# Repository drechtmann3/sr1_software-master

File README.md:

sr1_software
============

All software for SR1

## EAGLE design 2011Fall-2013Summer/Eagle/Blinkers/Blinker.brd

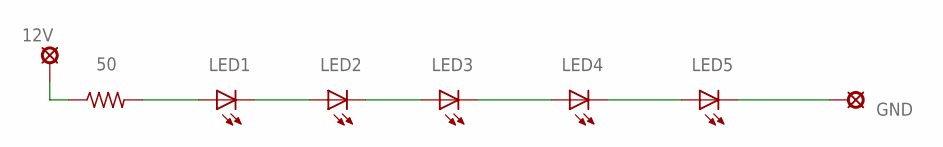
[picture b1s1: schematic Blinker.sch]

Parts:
12V: LSP13
50: RESISTORSMD1206; R1206
GND: LSP13
LED1: LED1; CP41B
LED2: LED2; CP41B
LED3: LED3; CP41B
LED4: LED4; CP41B
LED5: LED5; CP41B

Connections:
GND: GND.MP, LED5.1 (C), LED5.4 (C)
unnamed: 50.2, LED1.2 (A), LED1.3 (A)
unnamed: LED1.1 (C), LED1.4 (C), LED2.2 (A), LED2.3 (A)
unnamed: LED2.1 (C), LED2.4 (C), LED3.2 (A), LED3.3 (A)
unnamed: LED3.1 (C), LED3.4 (C), LED4.2 (A), LED4.3 (A)
unnamed: LED4.1 (C), LED4.4 (C), LED5.2 (A), LED5.3 (A)
unnamed: 12V.MP, 50.1

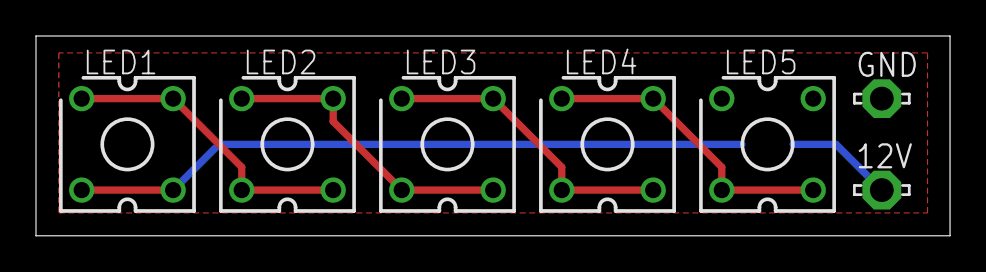
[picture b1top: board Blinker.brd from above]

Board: 2 copper layers, 50.8 x 11.1 mm, 8 parts (1 on the bottom side), 7 nets.

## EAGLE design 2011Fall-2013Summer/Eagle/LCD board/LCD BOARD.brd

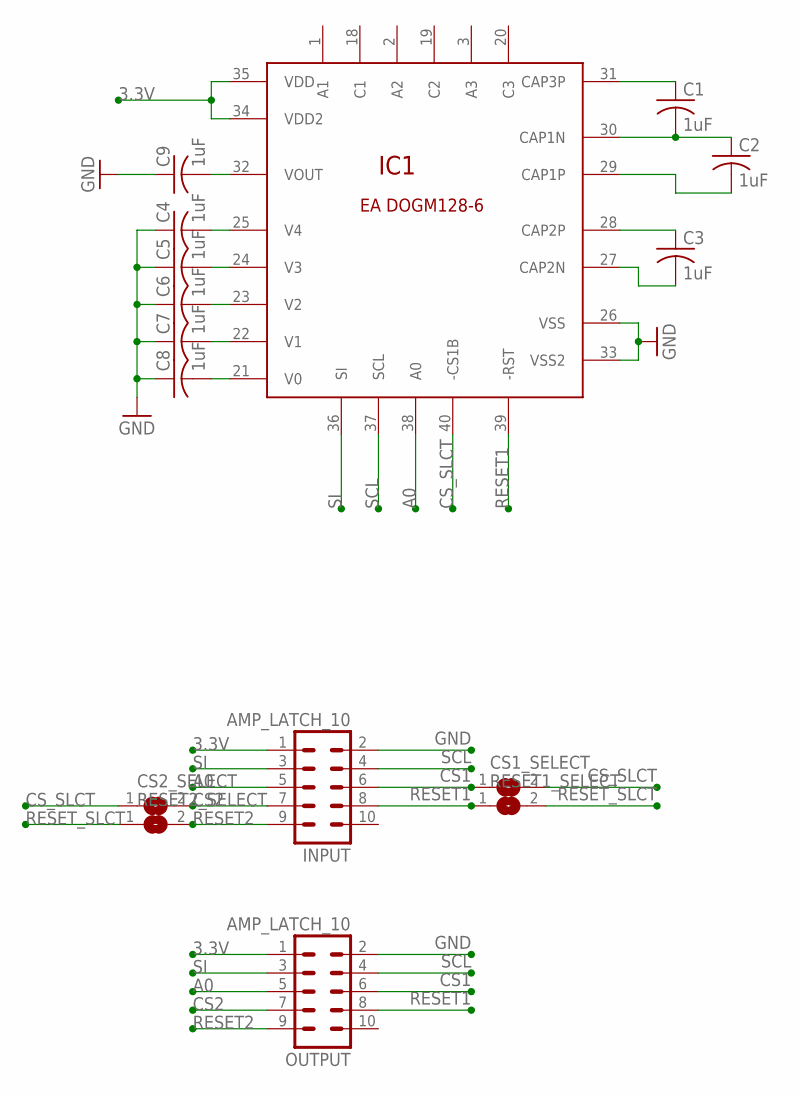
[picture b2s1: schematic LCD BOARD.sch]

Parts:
C1, C2, C3, C4, C5, C6, C7, C8, C9: 1uF; C1206
CS1_SELECT, CS2_SELECT: SJ
IC1: EADOGM128
INPUT: AMP_LATCH_10; MA05-2
OUTPUT: AMP_LATCH_10; MA05-2
RESET1_SELECT, RESET2_SELECT: SJ

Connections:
3.3V: IC1.34 (VDD2), IC1.35 (VDD), INPUT.1, OUTPUT.1
A0: IC1.38 (A0), INPUT.5, OUTPUT.5
CS1: CS1_SELECT.1, INPUT.6, OUTPUT.6
CS2: CS2_SELECT.2, INPUT.7, OUTPUT.7
CS_SLCT: CS1_SELECT.2, CS2_SELECT.1, IC1.40 (-CS1B)
GND: C4.1, C5.1, C6.1, C7.1, C8.1, C9.1, IC1.26 (VSS), IC1.33 (VSS2), INPUT.2, OUTPUT.2
unnamed: C1.2, C2.1, IC1.30 (CAP1N)
unnamed: C1.1, IC1.31 (CAP3P)
unnamed: C2.2, IC1.29 (CAP1P)
unnamed: C3.2, IC1.27 (CAP2N)
unnamed: C3.1, IC1.28 (CAP2P)
unnamed: C9.2, IC1.32 (VOUT)
unnamed: C4.2, IC1.25 (V4)
unnamed: C5.2, IC1.24 (V3)
unnamed: C6.2, IC1.23 (V2)
unnamed: C7.2, IC1.22 (V1)
unnamed: C8.2, IC1.21 (V0)
RESET1: IC1.39 (-RST), INPUT.8, OUTPUT.8, RESET1_SELECT.1
RESET2: INPUT.9, OUTPUT.9, RESET2_SELECT.2
RESET_SLCT: RESET1_SELECT.2, RESET2_SELECT.1
SCL: IC1.37 (SCL), INPUT.4, OUTPUT.4
SI: IC1.36 (SI), INPUT.3, OUTPUT.3

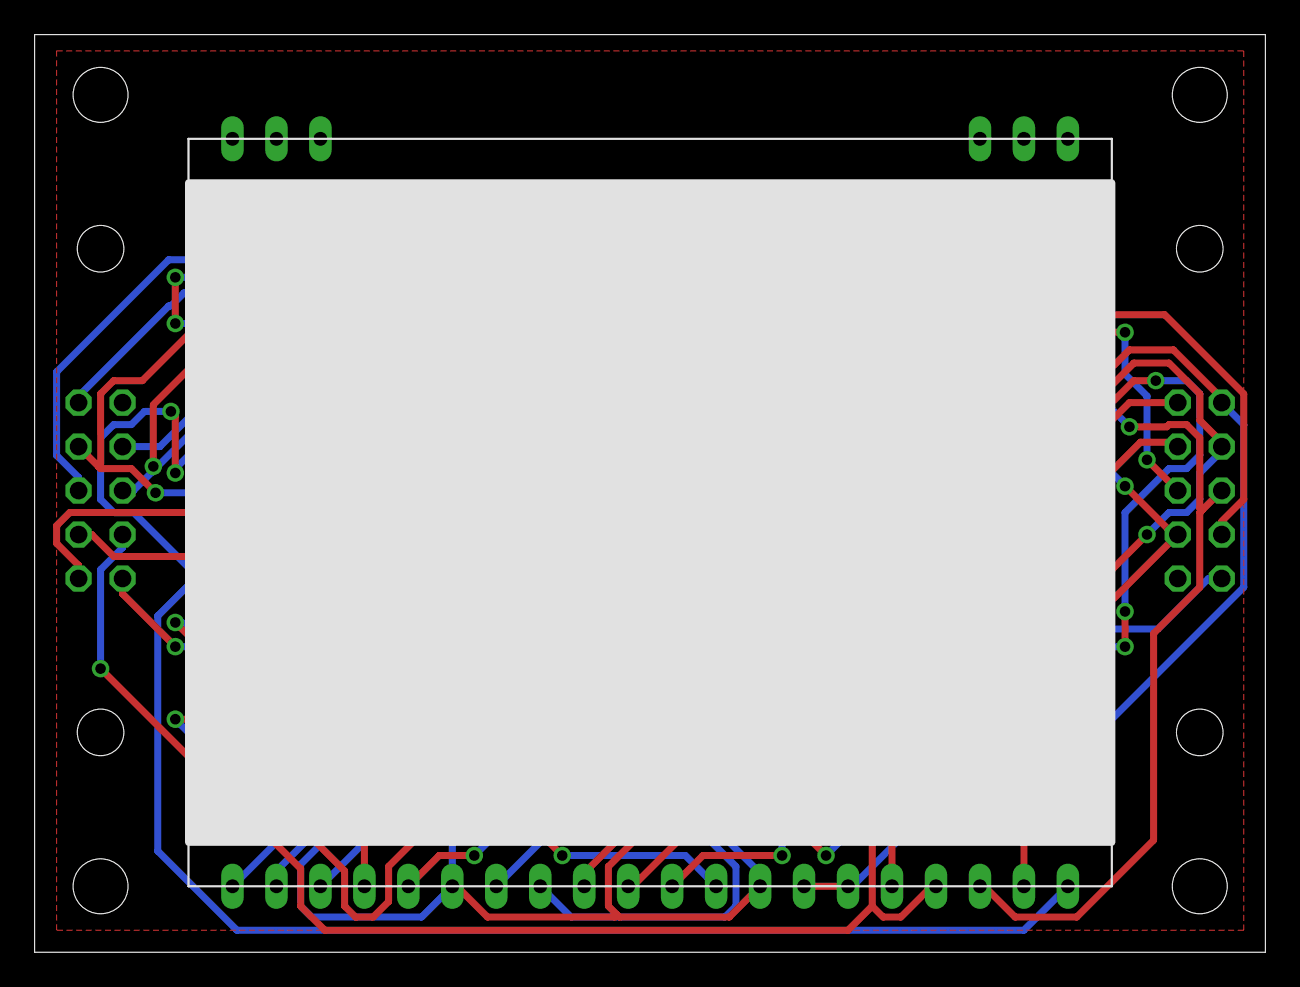
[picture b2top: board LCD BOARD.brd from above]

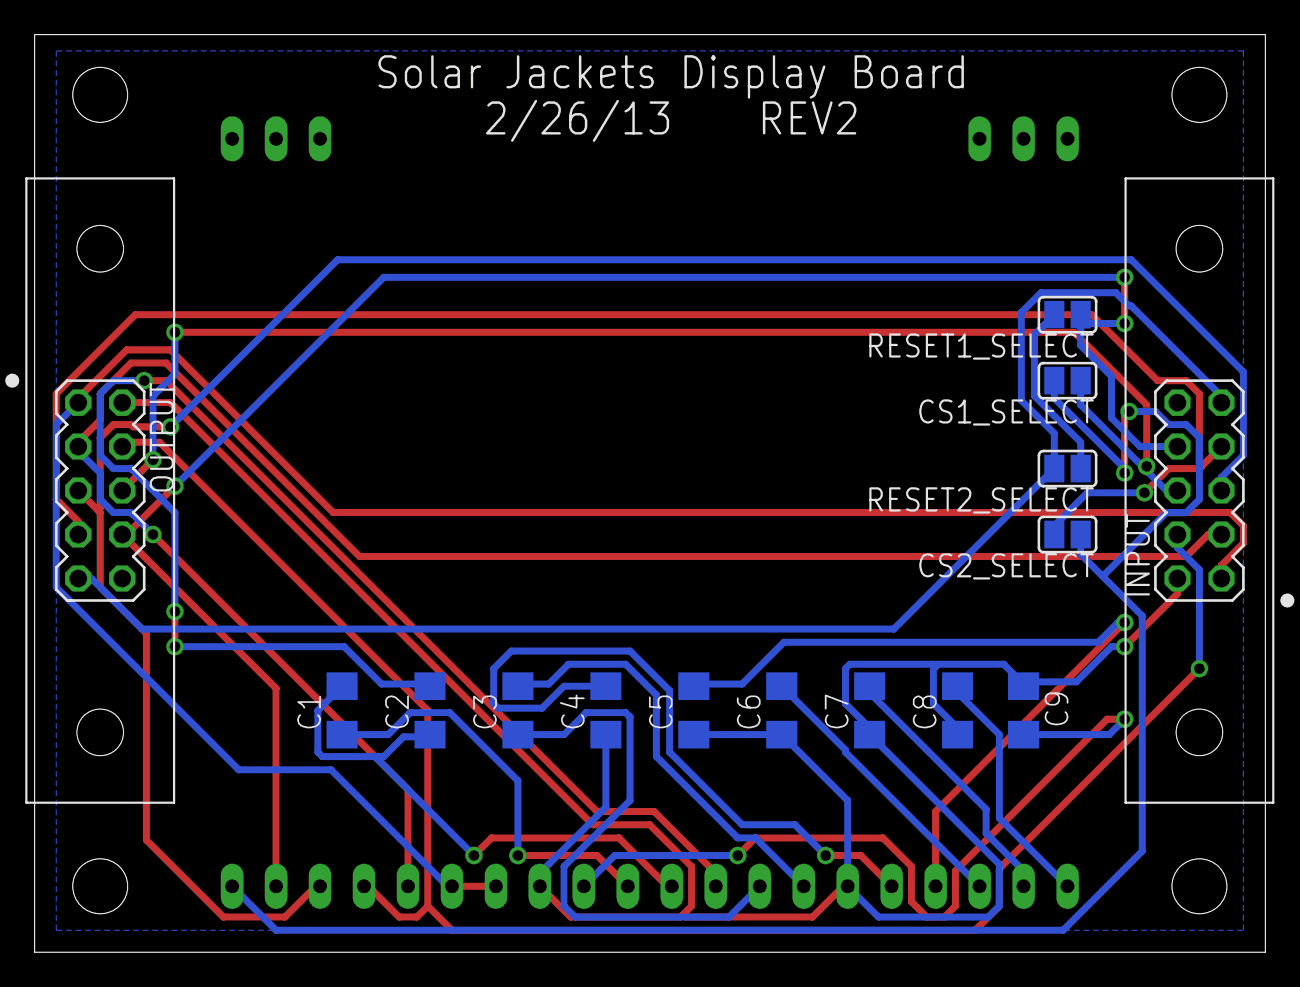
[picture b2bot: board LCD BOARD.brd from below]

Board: 2 copper layers, 71.1 x 53.0 mm, 16 parts (15 on the bottom side), 22 nets.
